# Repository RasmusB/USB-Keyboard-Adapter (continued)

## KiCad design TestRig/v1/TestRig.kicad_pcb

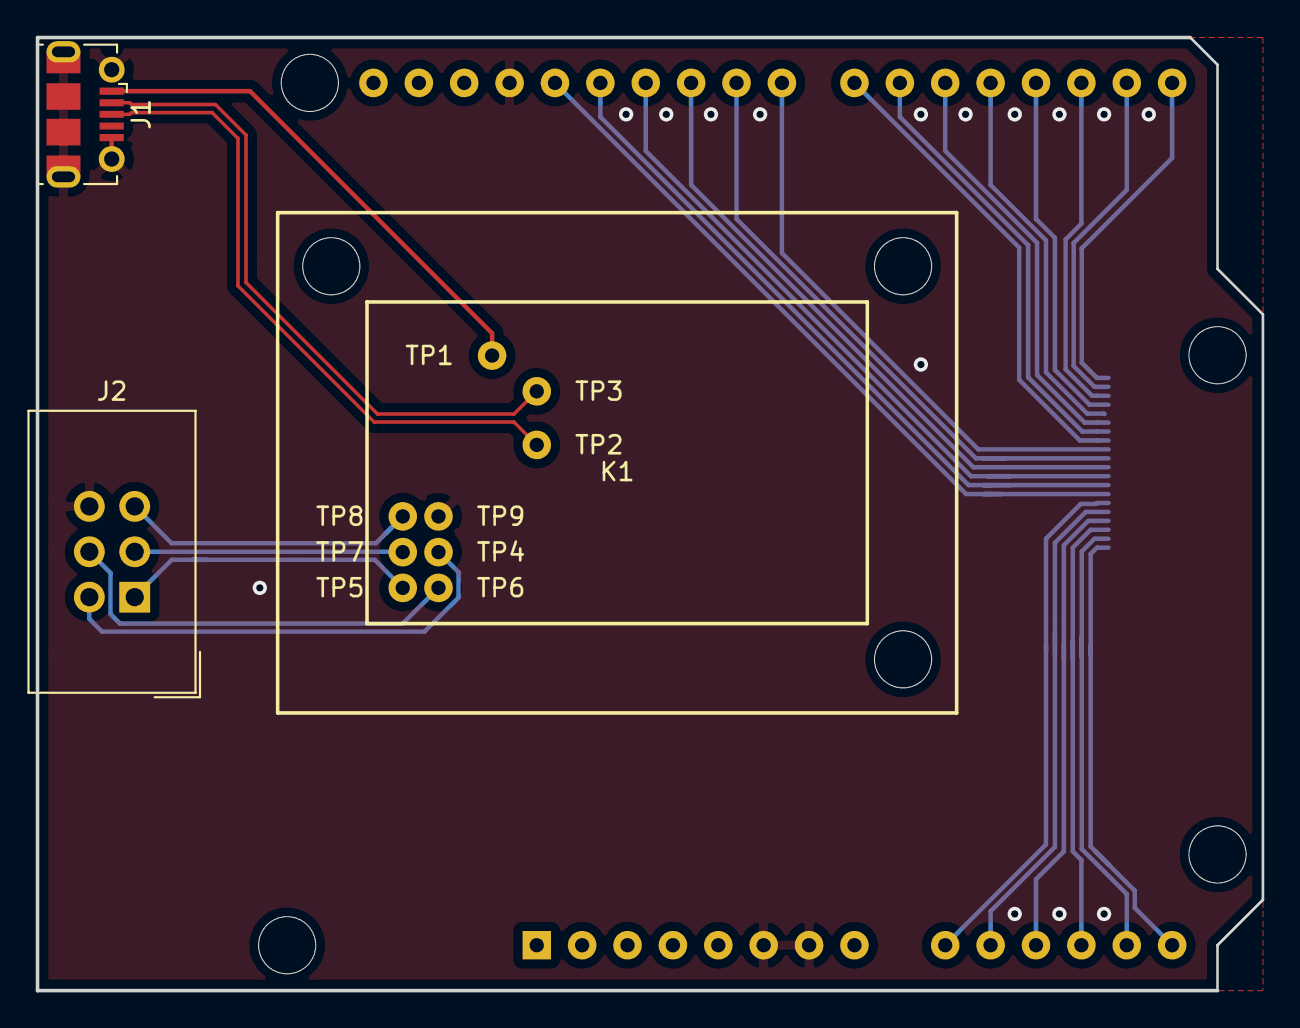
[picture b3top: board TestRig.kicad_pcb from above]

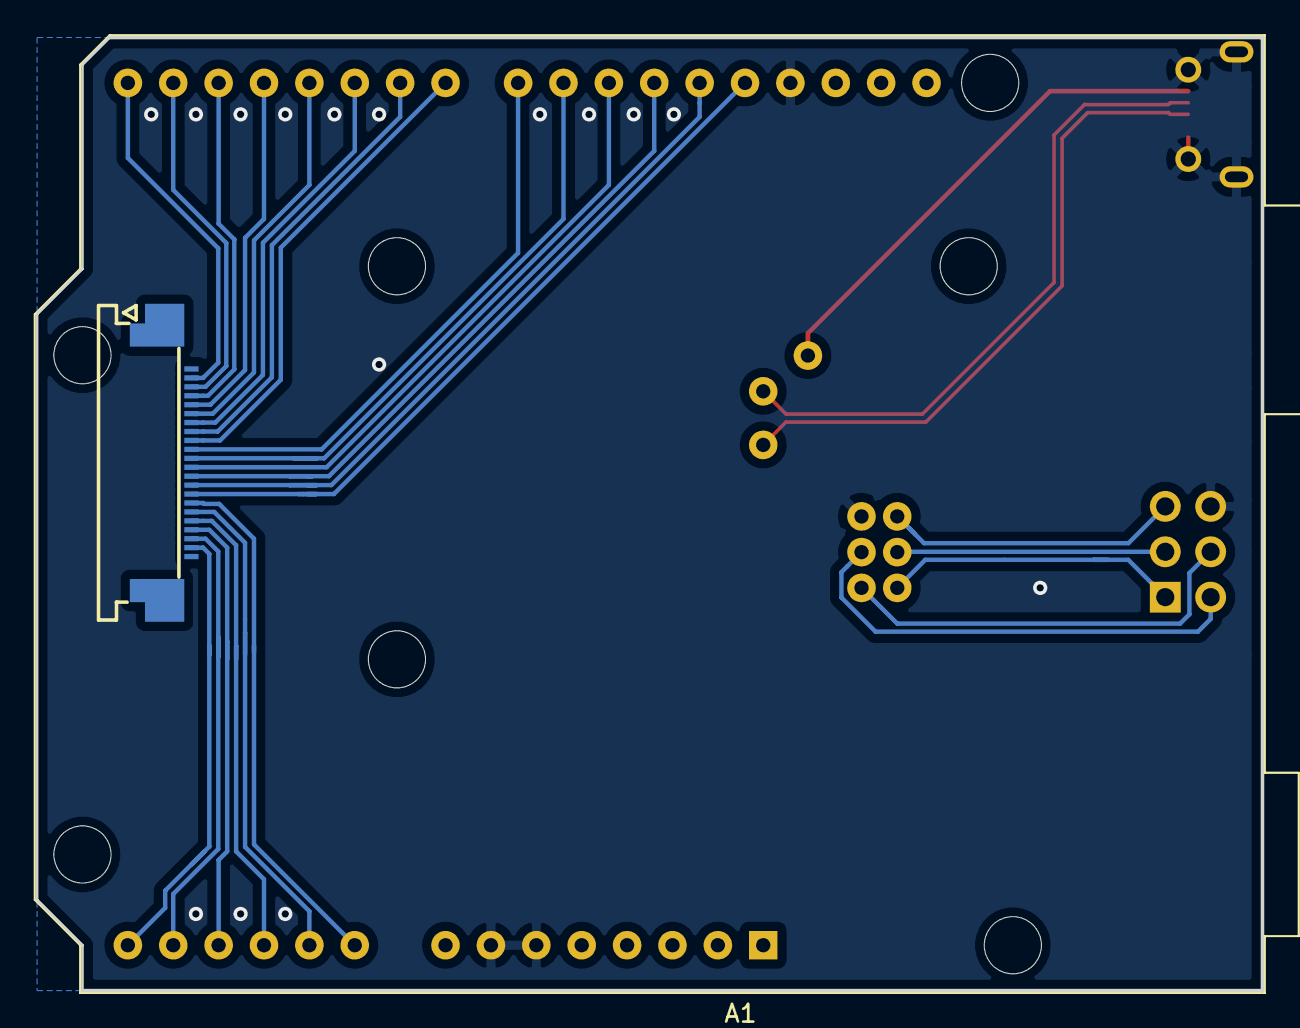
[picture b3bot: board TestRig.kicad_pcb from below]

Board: 2 copper layers, 68.6 x 53.3 mm, 18 parts (2 on the bottom side), 29 nets.

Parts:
A1: Arduino_UNO_R3; Arduino_UNO_R3_WithMountingHoles
J1: USB_B_Micro; USB_Micro-B_Molex-105017-0001
J2: AVR-ISP-6; IDC-Header_2x03_P2.54mm_Vertical
J3: To DUT; FPC_0.5mm_22p-MOLEX_52437
K1: PCB Jig 3D model; PCB_JIG
K2: 3D Model Dummy; USB_KEYBOARD_ADAPTER_V1.22_DUMMY
MH1, MH2, MH3: MountingHole; MountingHole_3.2mm_M3
TP1: VBUS; Mill-Max_7911-0-15-20-86-14-11-0
TP2: USB_D+; Mill-Max_7911-0-15-20-86-14-11-0
TP3: USB_D-; Mill-Max_7911-0-15-20-86-14-11-0
TP4: VCC; Mill-Max_7911-0-15-20-86-14-11-0
TP5: MISO; Mill-Max_7911-0-15-20-86-14-11-0
TP6: MOSI; Mill-Max_7911-0-15-20-86-14-11-0
TP7: SCK; Mill-Max_7911-0-15-20-86-14-11-0
TP8: ~RST; Mill-Max_7911-0-15-20-86-14-11-0
TP9: GND; Mill-Max_7911-0-15-20-86-14-11-0

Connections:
/D+: J1.3, TP2.1
/D-: J1.2, TP3.1
/FPC1: A1.15, J3.2
/FPC2: A1.16, J3.3
/FPC3: A1.17, J3.4
/FPC4: A1.18, J3.5
/FPC5: A1.19, J3.6
/FPC6: A1.20, J3.7
/FPC7: A1.21, J3.8
/FPC8: A1.22, J3.9
/FPC9: A1.23, J3.10
/FPC10: A1.24, J3.11
/FPC11: A1.25, J3.12
/FPC12: A1.26, J3.13
/FPC13: A1.27, J3.14
/FPC14: A1.28, J3.15
/FPC15: A1.9, J3.16
/FPC16: A1.10, J3.17
/FPC17: A1.11, J3.18
/FPC18: A1.12, J3.19
/FPC19: A1.13, J3.20
/FPC20: A1.14, J3.21
/MISO: J2.1, TP5.1
/MOSI: J2.4, TP6.1
/SCK: J2.3, TP7.1
/~RST: J2.5, TP8.1
GND: A1.6, A1.7, A1.29, J1.5, J1.6, J2.6, TP9.1
VBUS: J1.1, TP1.1
VCC: J2.2, TP4.1

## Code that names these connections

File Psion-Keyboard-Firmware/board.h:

/*
 board.h
 
 This is how the pins are connected to the keyboard
 
 */

// Fix for iPhone shutting down the board and reporting excess current draw
// The fix is to promise to not draw more than 100mA 
#undef D_CONFIG
#define D_CONFIG(_totalLength,_interfaces) \
    { 9, 2, _totalLength,_interfaces, 1, 0, USB_CONFIG_BUS_POWERED | USB_CONFIG_REMOTE_WAKEUP, USB_CONFIG_POWER_MA(100) }


// This disables the RX and TX LEDs that are not on this PCB
#undef TXLED0
#undef RXLED0
#undef TXLED1
#undef RXLED1
#undef TX_RX_LED_INIT

#undef LED_BUILTIN_RX
#undef LED_BUILTIN_TX

#define TXLED0 0
#define RXLED0 0 
#define TXLED1 0
#define RXLED1 0
#define TX_RX_LED_INIT 0


#define LED_BUILTIN_RX 0
#define LED_BUILTIN_TX 0


// Standard LED is moved to pin 11
#undef LED_BUILTIN
#define LED_BUILTIN 11
 
// See the keyboard schematic for row/col mapping
#define NROWS 8
#define NCOLS 12

#define ROW_01  22
#define ROW_02  20
#define ROW_03  5
#define ROW_04  13
#define ROW_05  18
#define ROW_06  21
#define ROW_07  7
#define ROW_08  23

#define COL_1   19
#define COL_2   10
#define COL_3   9
#define COL_4   8
#define COL_5   6
#define COL_6   12
#define COL_7   4
#define COL_8   30
#define COL_9   3
#define COL_10  1
#define COL_11  0
#define COL_12  2

int Rows [NROWS] = {
  ROW_01,
  ROW_02,
  ROW_03,
  ROW_04,
  ROW_05,
  ROW_06,
  ROW_07,
  ROW_08
};

int Cols [NCOLS] = {
  COL_1,
  COL_2,
  COL_3,
  COL_4,
  COL_5,
  COL_6,
  COL_7,
  COL_8,
  COL_9,
  COL_10,
  COL_11,
  COL_12
};

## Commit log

2017-02-22 Changed to top mount USB connector
    This will make the production a lot easier
2017-02-22 V1.1 prototype
    Ordered as is from OSHPark and OSHStencils
2017-03-21 Final version 1.1
    Tested and works as expected!
2017-04-05 Fixed Arduino sketches for v1.1 board
    Fixes issue #1
2018-06-07 Added bootloader and script for flashing
2018-06-12 Almost enables Delete
    Added UK Linux layout
2018-09-19 Updated to KiCAD 5
2018-09-19 Restore production files
    I discovered that I had overwritten the PCB files by accident. These are restored from an older version.
2018-09-19 Convert to KiCAD 5
    Updated to KiCAD version 5, regenerated board file copper pours
2018-09-21 Switched to new library names
    At least for the PCB
2018-09-26 Added test points
    For ICSP and USB. Keyboard connections are tested through a flex cable. LEDs are tested visually.
2018-09-26 Final fixes
    Re-annotation, version numbering of schematic
2018-09-26 Started work on test rig
    Missing 3D printed parts and correct footprints for whatever pogo pin I'd like to use
2018-10-05 Adjustments to PCB
2018-10-05 Should be done
2018-10-05 Should...
2018-10-05 Merging...
2019-03-06 Version 1.22 release
    Small layout fix. ISP header changed to SMD test points.
2019-10-23 Minor updates
2019-10-23 Moved old TestRig Files to v01 folder
2019-11-12 Current negotiation changed
    This causes the Arduino to not request more than 100mA of current.
2021-12-29 Adds working test rig
2022-08-31 Version 1.3 produced
